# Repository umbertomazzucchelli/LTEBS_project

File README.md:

# Electronic Technologies and Biosensors Laboratory

## Academic Year 2021/2022 - II Semester

## Final Project - Project 4 - Respiratory/Heart Rate Monitor

## Objective

In this project, the aim was to develop a simple **Respiratory/Heart Rate Monitor** based on the PSoC and a 3-axis accelerometer LIS3DH. The device implements an algorithm for respiratory and heart rate computation, and then it allows data visualization on a custom GUI. PSOC and PC communication relies on a HC-05 BT Module either to make the device wearable and to reduce the cable bulkyness.
The PSoC communicates with the LIS3DH thanks to I2C communication, to acquire data at the best full-scale range possible, which has been set to $\pm 2G$, and with sampling frequency of 50 Hz.  
Finally, the whole PCB is powered thanks to a 9V battery, which allows the device to be portable and light. 

In the following image, the device is shown: 

## Repository structure

### Design files

This folder contains all the projects used to model and 3D print the case and the chest mount for the sensor, along with the Eagle files, used to design the PCB. 

### Documentation

This folder contains the literature analysed during the development of the project, while the *Datasheets* folder contains all the datasheets for the components with some other useful files. 

### GUI

The GUI folder contains all the files necessary to run the graphical interface, which is the following:

The *device search* button enables the automatic scan of all the serial ports, looking for the device. As soon as it finds it, the connection is established and the box on the right becomes green, confirming the operation. The *combobox* allows to choose to read both HR and RR or only one of them. Calibration must be performed the first time that the device is worn, so that the algorithm computes the proper threshold to detect the rates. Once calibration is over (1 min approx.), the algorithm starts to accumulate data and to calculate the peaks from the signal, in order to compute RR and HR.

The *file* button allows to export the data in a `.csv` file. This operation will be automatically performed if the device is suddenly disconnected, so that the data is not lost. 

Heart Rate and Respiratory Rate are computed on non overlapping recording windows of 30s. Raw data are filtered and analysed in two different way for the computation of the rates. 

### Heart Rate computation

First, the absolute value of recorded data is filtered by a butter bandpass filter of the 4th order with frequency range in [1 ,5]Hz. The resulting signal is then smoothed first by a Savitzky-Golay filter of the 3rd order with window length of 15 samples and then by a moving average. These steps provide a resulting waveform that crearly shows the heart beats while being quite robust against noise.  
The next step provides the threshold as the 80% of the average of the data. The algorithm looks for the peaks above the calculated threshold that are at least 25 samples apart, that correspond to 0.5s approx.  
Finally, the Heart Rate is computed as the fraction between the number of peaks in the recorded window and the length of the window in seconds. This value is updated every 30s approx.

### Respiratory Rate computation

The computation of the Respiratory Rate requires different filtering of the signal.  
First, recorded data go through a butter lowpass filter of the 5th orded with cutoff frequency of 3Hz. This filtered signal is then smoothed by a Savitzky-Golay filter with a window of 31 samples and 3rd order. The threshold is calculated in the same way as in the HR computation, but the peaks are searched every 50 samples. 
The Respiratory Rate is calculated in the same way as the Heart Rate.

### iAcc.exe Software

The file iAcc.exe is an executable software which provides the functionalities of the implemented GUI. 

### Images

Images used for this `readme` file.

### PSoC

The *PSoC Code* folder contains all the files used to program the PSoC: in particular, all the functions and variables have been reordered in the proper file, allowing to increase the main.c file readibility.  
This code basically sets the proper configuration for the accelerometer registers at startup, making it ready for the data acquisition. All the different phases are managed thanks to a UART, that enables the different operations, according to the signals that come from the GUI. So, at the beginning the accelerometer is set and ready, once the PSoC receives the *start* signal from the GUI it begins to acquire data and to transmit them.  

Regarding the data acquisition, as previously mentioned the accelerometer has been set to a sampling frequency of 50 Hz, according to the Shannon's theorem and to the literature. In addition to that, the accelerometer operates in **FIFO mode**, so it accumulates all the samplings in the FIFO register (which contains up to 32 samples) and then it stops getting new data until the register has been emptied, allowing to reduce the computational load on the CPU and so the battery consumption, with respect to **bypass** mode, that sends the data in a continuous stream.  
In order to read the FIFO register, the PSoC checks regularly the value of the *overrun bit*, that becomes 1 once the FIFO register is full and returns to 0 when it has been entirely read.  
Once the `ovrn bit` changes to one, the register is entirely read, storing the data in the respective axis array. Then, the data is packed in one single array and sent via UART.

*Further implementation details can be found in each file.*

## Complete hardware list

- 1 PSoC CY8CKIT-059 
- 1 LIS3DH accelerometer
- 1 HC05 Bluetooth module
- 1 9V battery
- 1 9V to 5V voltage regulator 
- 6 cables for the accelerometer-PSoC communication

## How to wear the device

The 3D files for the case and the support can be found in the Design folder.

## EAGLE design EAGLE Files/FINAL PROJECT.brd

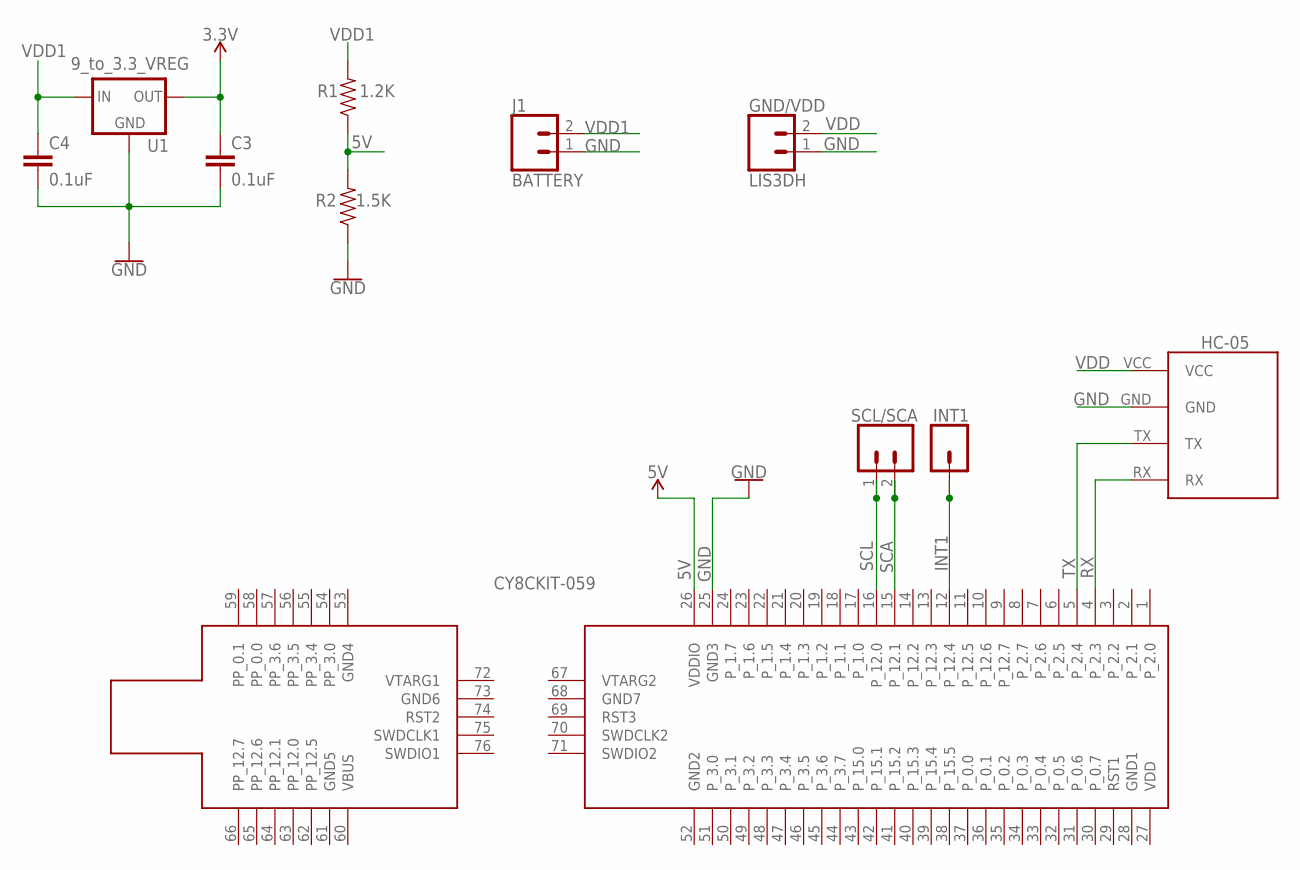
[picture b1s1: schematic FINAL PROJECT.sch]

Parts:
C3, C4: 0.1uF; CAP-PTH-SMALL-KIT
GND/VDD: LIS3DH; 1X02
HC-05: BLUETOOTH_BOARD; BT_BOARD_FOOTPRINT
INT1: CONN_01; 1X01
J1: BATTERY; 1X02
R1: 1.2K; AXIAL-0.3
R2: 1.5K; AXIAL-0.3
SCL/SCA: CONN_02; 1X02
U1: 9_to_3.3_VREG; TO-92
U$1: CY8CKIT-059

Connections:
5V: R1.P$1 (1), R2.P$2 (2), U$1.26 (VDDIO)
GND: C3.2, C4.2, GND/VDD.1, HC-05.GND, J1.1, R2.P$1 (1), U1.2 (GND), U$1.25 (GND3)
INT1: INT1.1, U$1.12 (P_12.4)
RX: HC-05.RX, U$1.4 (P_2.3)
SCA: SCL/SCA.2, U$1.15 (P_12.1)
SCL: SCL/SCA.1, U$1.16 (P_12.0)
TX: HC-05.TX, U$1.5 (P_2.4)
VDD: C3.1, GND/VDD.2, HC-05.VCC, U1.1 (OUT)
VDD1: C4.1, J1.2, R1.P$2 (2), U1.3 (IN)

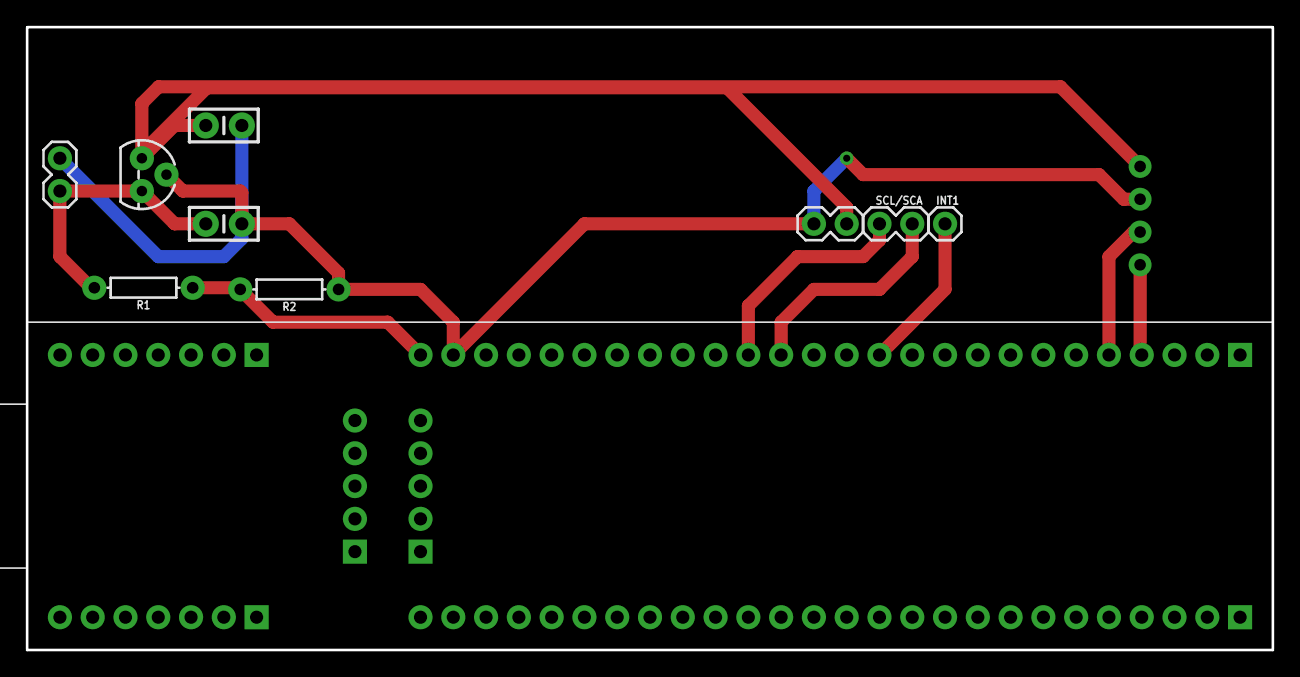
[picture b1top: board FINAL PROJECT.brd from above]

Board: 2 copper layers, 96.5 x 48.3 mm, 11 parts (1 on the bottom side), 9 nets.

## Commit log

2022-05-09 Added base .gitignore
2022-05-17 Repo init
2022-05-18 Acc reading fixed
2022-05-18 update - EAGLE files
2022-05-18 Added UART interrupt
2022-05-19 added EEPROM code
2022-05-19 EEPROM code
2022-05-19 error
2022-05-20 fixed FS and So management
2022-05-20 FS and So code
2022-05-20 configuration status
2022-05-20 fixed initialization
2022-05-20 GUI update
2022-05-22 GUI automatic connection fixed + started data transfer coding
2022-05-23 useless files removed
2022-05-23 minor changes, GUI updated
2022-05-23 EAGLE-Files-added LED
2022-05-23 LED fixed
2022-05-23 LED-fixed
2022-05-23 button fixed
2022-05-24 3D printer files added
2022-05-25 GUI-QTDesigner
2022-05-25 connection fixed
2022-05-25 Data reading fixed
2022-05-26 reading fixed, all data is divided in the three axis arrays
2022-05-26 final EAGLE files
2022-05-26 graph
2022-05-28 data graph updated
2022-05-29 filters
2022-05-29 Untrack files in .gitignore
2022-05-29 graph up
2022-05-29 bug solved
2022-05-30 Fixed BT transmission
2022-05-30 added GUI with save status
2022-05-30 added icon to gui
2022-05-31 little update to interface
2022-05-31 board
2022-06-01 Changed data reading
2022-06-05 Removed all files that are in the .gitignore
2022-06-06 disabled mouse interaction - gui
2022-06-06 FSR implementation
2022-06-08 Filters update
2022-06-10 autocalibration stage and float array
2022-06-18 Data rescaling completed
2022-06-19 Reordered the code
2022-06-20 Added calibration function
2022-06-23 Interface updated
2022-06-23 Filters and interface
2022-06-27 Pavi
2022-06-28 export in csv file
2022-06-29 RR algorithm
2022-06-29 Algorithm's Updates
2022-06-29 software not ready
2022-07-01 updated code new GUI
2022-07-01 Documentation and Literature re-added
2022-07-01 Algorithm improvements
2022-07-03 update literature
2022-07-03 new filtering functions and algorithms
2022-07-04 revert changes
2022-07-05 Clear
2022-07-05 Disconnection
2022-07-05 Warning
2022-07-06 error window fixed
2022-07-06 HR algorithm and bug fixing
2022-07-06 Improvements
2022-07-07 PSoC code cleaned and added some images for readme
2022-07-07 readme updated + repo reordered
2022-07-07 Algorithms and filtering completed
2022-07-07 Comments added
2022-07-07 Graph RR and HR
2022-07-08 GUI HR and GUI RR cleaned
2022-07-08 variables update
2022-07-08 files fixed
2022-07-08 files merged + minor fixes
2022-07-08 bug fixed
2022-07-08 Executable Software iAcc.exe
2022-07-08 last changes
2022-07-14 Added final presentation

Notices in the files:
parts and their libraries:
SparkFun-IC-Power: Licensing: Creative Commons ShareAlike 4.0 International - https://creativecommons.org/licenses/by-sa/4.0
